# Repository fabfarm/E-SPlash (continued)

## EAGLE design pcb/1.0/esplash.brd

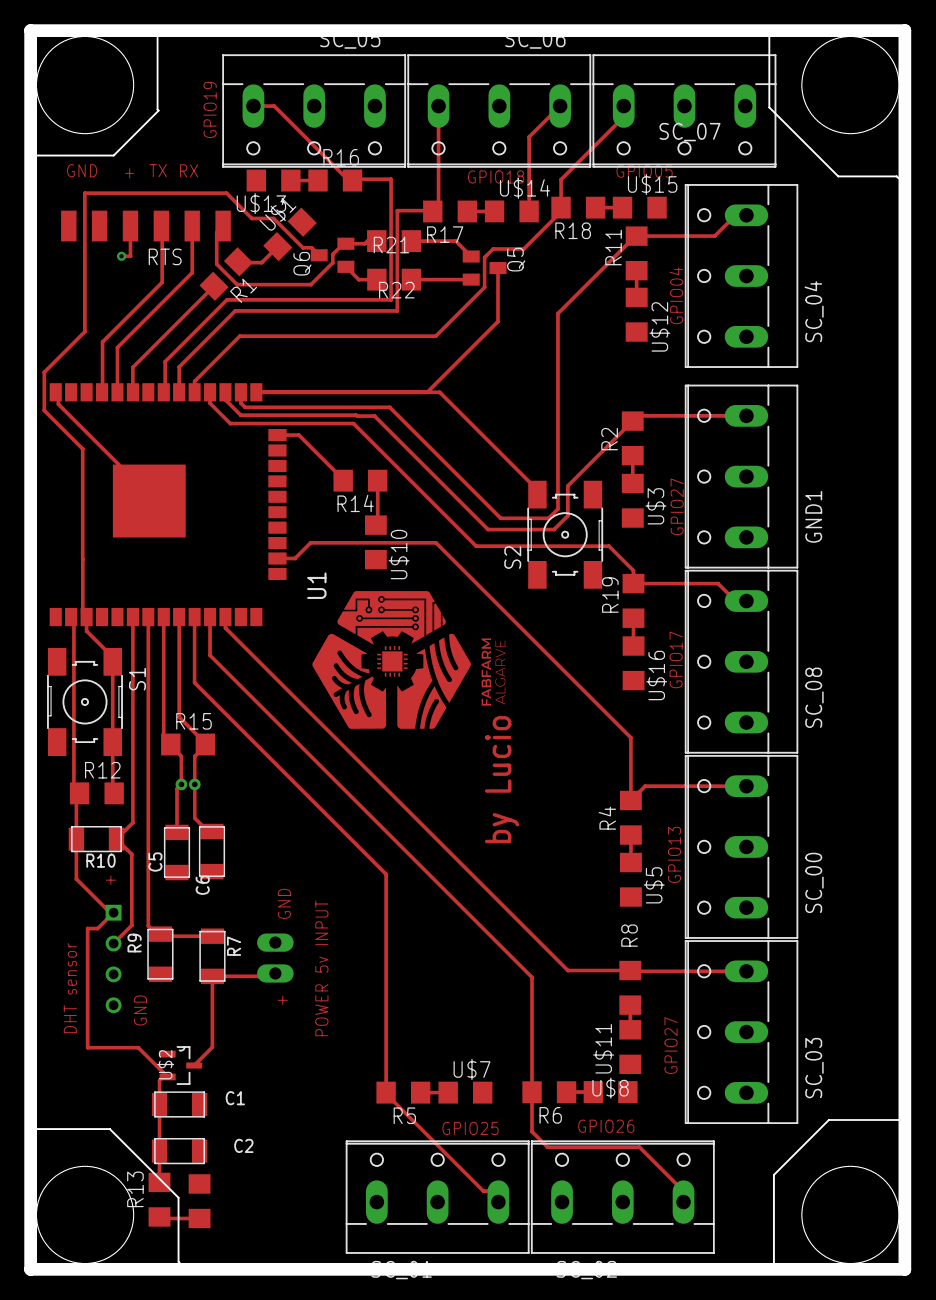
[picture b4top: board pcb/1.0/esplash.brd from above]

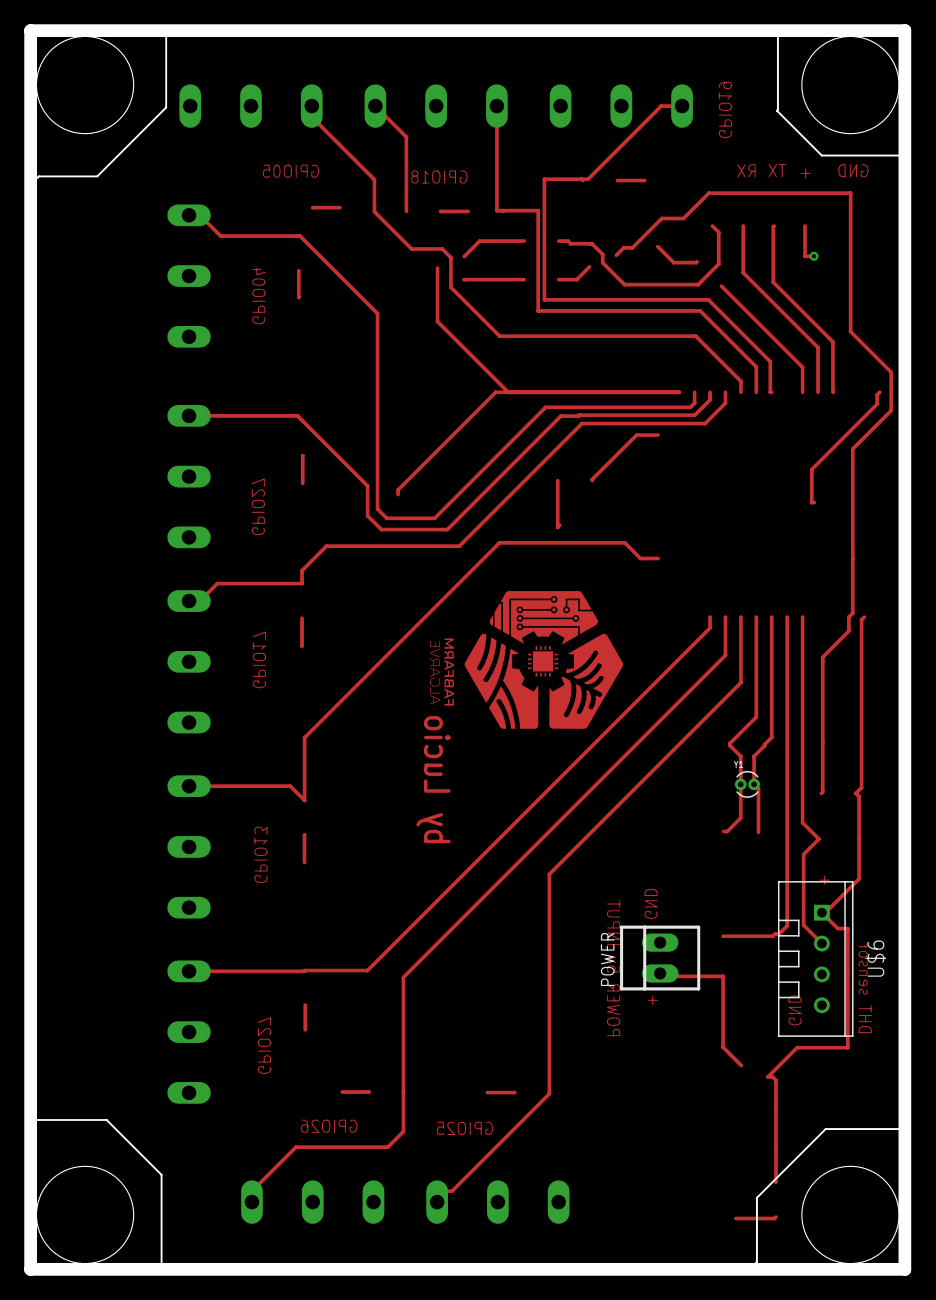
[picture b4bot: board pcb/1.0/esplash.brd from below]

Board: 2 copper layers, 72.0 x 102.0 mm, 57 parts (3 on the bottom side), 40 nets.

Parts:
C1: 100nF; C1206FAB
C2: 100uF; C1206FAB
C5, C6: 15pf; C1206FAB
GND1: SC; W237-103
POWER: 22-23-2021
Q5, Q6: BCX70SMD; SOT23
R1, R2, R4, R5, R6, R8, R11, R13, R14, R16, R17, R18, R19: 100ohm; R1206
R7: 1.2Mohm; R1206FAB
R9: 1.5Mohm; R1206FAB
R10: 10K; R1206FAB
R12, R15, R21, R22: 10k; R1206
RTS: FTDI-SMD-HEADER; 1X06SMD
S1: Reset; 6MM_SWITCH
S2: GPIO0 Button; 6MM_SWITCH
SC_00, SC_01, SC_02, SC_03, SC_04, SC_05, SC_06, SC_07, SC_08: SC; W237-103
U1: ESP-WROOM-32
U$1, U$3, U$5, U$7, U$8, U$9, U$10, U$11, U$12, U$13, U$14, U$15, U$16: LED; LED1206
U$2: MCP1700T-3302E/TT; SOT95P237X112-3N
U$6: TEMP-HUM-SENSOR-DHT11
Y1: ECS-.327-12.5-13X; XTAL_ECS-.327-12.5-13X

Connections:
3V3: C1.2, C2.1, R10.2, R12.1, R13.2, U1.2, U$2.2, U$6.1
32K_XN: C6.2, R15.2, U1.9, Y1.1
32K_XP: C5.2, R15.1, U1.8, Y1.2
CHIP_PU: Q6.3, R12.2, S1.1, S1.2, U1.3
DTR: Q5.2, R22.2
GND: C1.1, C2.2, C5.1, C6.1, GND1.1, POWER.2, R9.1, RTS.1, S1.3, S1.4, S2.3, S2.4, SC_00.1, SC_01.1, SC_02.1, SC_03.1, SC_04.1, SC_05.1, SC_06.1, SC_07.1, SC_08.1, U1.1, U1.15, U1.38, U1.GND, U$1.2, U$2.1, U$3.2, U$5.2, U$6.4, U$7.2, U$8.2, U$9.2, U$10.2, U$11.2, U$12.2, U$13.2, U$14.2, U$15.2, U$16.2
GPIO0: Q5.3, S2.1, S2.2, U1.25
GPIO1/TXD0: RTS.4, U1.35
GPIO02: R14.2, U1.24
GPIO3/RXD0: RTS.5, U1.34
GPIO4: R11.2, SC_04.3, U1.26
GPIO05/VALVE_RELAY07: R18.2, SC_07.3, U1.29
GPIO13/PUMP_RELAY: R4.2, SC_00.3, U1.16
GPIO16/CURRENT_SENSE: GND1.3, R2.2, U1.27
GPIO17/VALVE_RELAY08: R19.2, SC_08.3, U1.28
GPIO18/VALVE_RELAY06: R17.2, SC_06.3, U1.30
GPIO19/VALVE_RELAY05: R16.2, SC_05.3, U1.31
GPIO21/VALVE_RELAY04: R1.2, U1.33
GPIO25/VALVE_RELAY01: R5.2, SC_01.3, U1.10
GPIO26/VALVE_RELAY02: R6.2, SC_02.3, U1.11
GPIO27/VALVE_RELAY03: R8.2, SC_03.3, U1.12
GPIO34/DHT: R10.1, U1.6, U$6.2
GPIO35/BATTVOLT: R7.1, R9.2, U1.7
unnamed: R1.1, U$1.1
unnamed: R2.1, U$3.1
unnamed: R14.1, U$10.1
unnamed: R4.1, U$5.1
unnamed: R5.1, U$7.1
unnamed: R6.1, U$8.1
unnamed: R8.1, U$11.1
unnamed: R11.1, U$12.1
unnamed: R16.1, U$13.1
unnamed: R13.1, U$9.1
unnamed: Q5.1, R21.1
unnamed: R17.1, U$14.1
unnamed: R18.1, U$15.1
unnamed: R19.1, U$16.1
unnamed: Q6.1, R22.1
RTS: Q6.2, R21.2, RTS.6
VCC: GND1.2, POWER.1, R7.2, RTS.3, SC_00.2, SC_01.2, SC_02.2, SC_03.2, SC_04.2, SC_05.2, SC_06.2, SC_07.2, SC_08.2, U$2.3

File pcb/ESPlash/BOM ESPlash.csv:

Value,Coluna1,Package,Description,Qty,Unit Price,Total Price
PCB blank,,," Proto Board Copper Clad FR1, Single Sided, 1 oz. 5.00"" x 4.00"" (127.0mm x 101.6mm) ",1, $2.44 , $2.44 
FTDI-SMD-HEADER,,1X06SMD, CONN HEADER R/A 6POS 2.54MM ,1, $0.18 , $0.18 
22-23-2021,,22-23-2021, CONN HEADER VERT 2POS 2.54MM ,1, $0.17 , $0.17 
header2x6,,2X03, CONN HEADER VERT 6POS 2.54MM ,2, $0.48 , $0.96 
SWITCH,SWITCH,SWITCH TACTILE SPST-NO 50MA 12V,SWITCH TACTILE SPST-NO 50MA 12V,2, $0.20 , $0.40 
0.1uF ,Capacitor,C1206FAB, CAP CER 0.1UF 50V X7R 1206 ,2, $0.11 , $0.22 
100uF,Capacitor,C1206FAB, CAP CER 100UF 10V X5R 1206 ,1, $1.49 , $1.49 
15pf,Capacitor,C1206FAB, CAP CER 15PF 50V 1206 ,2, $0.19 , $0.38 
1nF,Capacitor,C1206FAB, CAP CER 1206 1NF 250V X7R 10% ,1, $0.27 , $0.27 
ESP32-WROOM-32 (16MB),,ESP-WROOM-32,WIFI MODULE 128MBITS SPI FLASH,1, $4.50 , $4.50 
LED,LED,LED1206,Standard LEDs - SMD 1206 Blue ,7, $1.45 , $10.15 
100ohm,Resistor,R1206,RES SMD 100 OHM 1% 1/4W 1206,5, $0.57 , $2.85 
10k,Resistor,R1206,RES SMD 10K OHM 1% 1/4W 1206,3, $0.57 , $1.71 
1.2Mohm,Resistor,R1206,RES SMD 1.2M OHM 1% 1/4W 1206,1, $0.10 , $0.10 
1.5Mohm,Resistor,R1206,RES SMD 1.5M OHM 1% 1/4W 1206,1, $0.18 , $0.18 
150ohm,Resistor,R1206,RES SMD 15 OHM 1% 1/4W 1206,2, $0.10 , $0.20 
1K,Resistor,R1206,RES SMD 1K OHM 1% 1/4W 1206,4, $0.57 , $2.28 
220omh,Resistor,R1206,RES SMD 220 OHM 1% 1/4W 1206,4, $0.10 , $0.40 
SRD-05VDC-SL-C,Relay,RELAY_SRD-05VDC-SL-C,SRD-5VDC-SL-C 5 Pin PCB Type,4, $1.99 , $7.96 
ACS712,,SO08, SENSOR CURRENT HALL 20A AC/DC ,1, $2.32 , $2.32 
,,SOD123, DIODE GEN PURP 100V 200MA SOD123 ,4, $0.13 , $0.52 
EL817(S)(D)(TU)-V,,SOIC254P1030X460-4N, OPTOISOLTR 5KV TRANSISTOR 4-DIP ,4, $0.18 , $0.72 
BCX70SMD,,SOT23, TRANS NPN 45V 0.1A SOT23 ,4, $0.19 , $0.76 
MCP1700T-3302E/TT,,SOT95P237X112-3N, IC REG LINEAR 3.3V 250MA SOT23-3 ,1, $0.37 , $0.37 
TEMP-HUM-SENSOR-DHT11,,TEMP-HUM-SENSOR-DHT11, SENSOR HUMID/TEMP 5V DTL 5% MOD ,1, $5.00 , $5.00 
,,W237-102,WAGO SCREW CLAMP,4, $0.10 , $0.40 
ECS-.327-12.5-13X,,XTAL_ECS-.327-12.5-13X,CRYSTAL 32.7680KHZ 12.5PF TH,1, $0.24 , $0.24 
,,,,, Total , $44.73

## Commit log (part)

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2020-06-14 new version compiling with external file system
2020-06-14 included code to show temp and humidity as well as time, all compiling
2020-06-15 Nnow we have time!
2020-06-16 function to turn time components like mins, hours etc into a variable
    I am still learning there must be an easier way :-)
2020-06-17 adding features into index.html. need help with JS bug
2020-06-18 Revert "Update README.md"
    This reverts commit 9f7c9a71d101eb58e78ddfe2259100fd16ccab90.
2020-06-18 Revert "updates"
    This reverts commit 29ba24a5f4c021fb44f9e41ddd7c0519eee81153.
2020-06-18 Revert "adding features into index.html. need help with JS bug"
    This reverts commit b84a338d112b8ed323edd0073b4a52574d56285e.
2020-06-20 Adding functions for get/save
2020-06-20 Adds AsyncJson to platform.io Not yet in use but may use for handling json server side
2020-06-21 POC for json serialize / deserialize
2020-06-21 Write json to disk Read json from disk Deserialize json & update values
2020-06-21 Proof of concept for json
2020-06-21 change data.jaon
    added states
2020-06-21 Callback work in progress
2020-06-21 json read/write
    SPIFFS having trouble with r/w file system
2020-06-22 Backend working
2020-06-22 html reading json
    - html file + js building page from json
2020-06-22 works
2020-06-23 some cleanning up
2020-06-23 Update formatting & comments
2020-06-23 Update formatting + comments
2020-06-23 fix typo
2020-06-23 fix bugs introduced from merges
2020-06-23 manual mode and schedule mode works now.
2020-06-24 progress save on scheduling
    need to break apart time and compare to current time
2020-06-24 last update of the night
2020-06-25 updates
    sucssessifully parsing the json to c++ already in int for the start time and duration
    matrix logic test tested! its good prints well all parameters
    next is to make the start logic
2020-06-26 dealing with issue #10
    -changed from while to if (WiFi.status() != WL_CONNECTED) and placed in the loop instead of setup adding a message for the case it connected.
    Tested i my setup it works.
    -added message of wich sone is active.
2020-06-26 now #6 is fixed
2020-06-27 #11 attempt to add pump on/offalong with valves
    - included pumpPin 33 and its declarations
    - Included digitalWrite on each case
    - modified names from override to isScheduleMode
    ps: its not working as expected, the pumpPin keps going low ... high ... low... high
    @jknight I know its bad code, need to sleep, will leave here safe at the hands of github...
2020-06-27 #14 removed unecessary reading of json...
2020-06-28 #11 Pump now enable / disables as expected.
2020-06-30 short delays
2020-07-02 PCB updates
2020-07-06 board
2020-07-16 creating enclosure
2020-11-02 remove delays
2021-04-29 trying to fix wifi bug and refresh bug
2021-04-30 Adding time without using internet
2021-05-01 PCB changes
2021-05-07 Html/ json communication fail
2021-05-10 new board
2021-05-10 update monitor speed
2021-05-11 Update fabfarm_irrigation.ino
    Changes suggested by @carlosmouracorreia in his commit 7e49d787ab5b9ebbfad36f8027c647d13e586848
2021-05-14 Solved the freezing time problem but need to reset each time the time is modified (to be improved)
2021-05-17 no freezing time without external declaration
    but still needs to reset for time change
2021-05-21 improving relay table in settup page
    improving relay table in settup page and updating sample json
2021-07-04 added support for relays with TTL Logic LOW and cleanup
    included option to use relays with TTL Logic LOW
    improve readability and cleanup
2021-07-19 adding support for DS3231
    Adding support for DS3231 and cleaning up
2021-07-25 separating java script from html and having fonts locally
2021-07-26 refreshing the time every second. side effect is that the slider is not as smooth. next step separate the script so only update what is needed.
2021-07-26 added function to write first json file in case it does not exist.
    added function to write data.json file in case it does not exists,
    It uses the file sample.json to create a first data.json file.
2021-08-04 small changes not tested
2021-08-20 test
2021-08-21 clean up old code
2021-08-24 fixing wifi bug that prevented from being connected from a smartphone
2021-08-24 created pcb profiles with if def and clean up code
    created pcb profiles with if def and clean up code removing function previously used to reconnect
2021-09-14 reduction of web page refresh rate from 1s to 10s and fix of the /getdata route by using a copy of jsondocument to serialize instead of a cast
2021-09-16 correcting parameters of prototype board
2021-09-19 Added a few credentials for wifi and changed DHT sensor settings
2022-02-07 (#0) Add properties
2022-02-14 (#0) Finish control page times basic feature. Still need validations
2022-02-25 (#0) Add funcitonailties
2022-03-03 Code review, consistent function names and documentation
2022-03-04 added ifdef for stactic IP
    added ifdef for stactic IP also removed a done todo
2022-03-07 Refactor WiFi configuration
2022-03-08 comments clearification.
2022-03-10 Move to a more RESTful Web API, improved refresh
    Use more REST aware endpoints
    Moved Scheduling Mode HTML element from JavaScript into the HTML file
    Use more REST aware endpoints
    Rewritten refresh method, tries to update live state with the least
    possible delay
2022-03-10 HTML validation results, local bootstrap
    Validated the HTML with w3c.org HTML Checker and solved found errors.
    Bootstrap library is now hosted from device, and not from Content
    Delivery Network.
    Moved Scheduling Mode HTML element from JavaScript into the HTML file
2022-03-10 Initial config.json file for future use
2022-03-10 Move to a more RESTful Web API
    Use more REST aware endpoints
2022-03-10 Fix rendering the relay times
2022-03-10 Move to Bootstrap, work in progress
2022-03-10 Improved serial print
2022-03-18 Fix and rework time scheduling code
2022-03-25 Fix bug in setting scheduling mode
2022-05-26 set lib versions in working versions
2022-05-27 fixed typo jason -> json
2022-06-16 adding multi wifi support
2022-06-24 change to battery sensing board
2023-02-19 better comments and struct for board selection
    modified board selection with struct to improve understanding of the code. improved and added comments
2023-02-19 JS updates
2023-06-14 resolve compileerror
2023-06-15 refactor WebServerHandle.cpp
2023-06-16 refactor WiFiHandler.cpp
2023-06-19 modify for litleFS, fix bug, refactor jsonHandler
2023-06-23 include elegantOTA
2023-06-23 increase time interval to refresh data
2023-07-10 resetting vite template
2023-07-10 Add main components
2023-07-10 add logo + testing github login
2023-07-10 Header comp; add logo; comp indexes;
2023-07-10 minor
2023-07-10 some dashboard styles
2023-07-11 test other reset libs
2023-07-11 tablet breakpoint
2023-07-11 sanitize.css; more styles;
2023-07-11 basic controls style and html
2023-07-11 more styles
2023-07-11 logo responsiveness
2023-07-12 add automatic time inputs
2023-07-12 removed individual manual-auto
2023-07-13 add Home page
2023-07-13 topbar router links
2023-07-16 controlsData; handle schedule mode checkbox;
2023-07-17 styling
2023-07-17 handleToggleRelay: updating state in nested object finally work
2023-07-18 WIP: set time btn onclick
2023-07-20 comments on functions to look at
2023-07-20 basic DateAndTime html and css
2023-07-20 wifi credentials html
2023-07-24 fetchSettingsData; updateTime and enableInternetUpdate
2023-07-24 WifiCredentials: updateCredentials;
2023-07-25 api-schema and data - WIP
2023-07-25 more api-schema - WIP
2023-07-25 mods and comments for new relay contro lbox design
2023-07-26 going back to orginal design
2023-07-26 star working on Settings page baased on old server
2023-07-26 fetch data - wip; services - wip;
2023-07-26 dashboard uses new data structure
2023-07-26 methods based on api-schema - WIP
2023-07-26 methods based on api-schema
2023-07-27 Relays
2023-07-28 api-schema and notes
2024-04-16 Temporary hotfix for ISR timeout until MR for ISR timeout with latest updates is available
2024-04-17 gitignore changes
2024-04-23 moving from AsyncElegantOTA to ElegantOTA due to the first is discontinued
2025-02-01 add version to arduinoJson to prevent breaking changes
2025-06-29 Hardware configuration cleanup: hard-coded relay pins in platformio.ini and simplified board config
    - Added relay pins as build flags: RELAY1_PIN=27, RELAY2_PIN=26, RELAY3_PIN=25, PUMP_PIN=13
    - Simplified BoardConfig to single configuration without hardware variants
    - Updated sample.json to use correct relay pins (27, 26, 25)
    - Ready for further simplification of relay management UI
2025-06-29 Add AI coding guidelines for project architecture
    - Emphasizes keeping main.cpp clean and modular
    - Prohibits delay() functions on ESP32 with web servers
    - Documents fixed hardware pin configuration
    - Establishes clear modular architecture rules
    - Provides specific do's and don'ts for future AI assistants
2025-06-29 Remove unused pin definitions from platformio.ini
    - Removed I2C_SDA_PIN and I2C_SCL_PIN (unused, I2C pins hardcoded in Config.cpp)
    - Removed RTC_IRQ_PIN (unused, no interrupt handling)
    - Removed BAT_VOLT_PIN (unused, no battery voltage monitoring)
    - Removed NUM_RELAYS (unused in codebase)
    - Simplified configurations to only include necessary GPIO pins for relay control
2025-06-29 Remove pin configuration from JSON - use hardcoded hardware pins
    - Removed initializeHardwarePins() function from JsonHandler
    - Updated RelayHandler to use hardcoded pins (RELAY1_PIN, RELAY2_PIN, RELAY3_PIN)
    - Removed pin fields from sample.json since pins are hardware-specific
    - Pins are now defined in platformio.ini and cannot be changed by users
    - This prevents configuration conflicts and enforces hardware constraints
2025-06-29 Optimize scheduling system with event-driven approach
    - Implement event-driven scheduling to eliminate serial output flooding
    - Add getNextScheduleEventTime() function to calculate next schedule events
    - Replace constant schedule checking with smart event-based triggers
    - Add state tracking to prevent redundant relay operations and logging
    - Implement smart frontend polling (10s/60s intervals based on schedule proximity)
    - Remove debug output spam from WebServerManager handleGetDataJsonRequest
2025-06-30 Remove OTA functionality from irrigation system
    - Deleted OTAHandler.h and OTAHandler.cpp files
    - Removed OTA includes from Config.h
    - Removed initializeOTA() and handleOTA() calls from main.cpp
    - Removed ArduinoOTA library dependency from platformio.ini
    - Simplified main loop by removing OTA active checks
    - Project now compiles successfully without OTA functionality
2025-06-30 feat: Complete UI redesign with modern agricultural theme and enhanced functionality
    🎨 Design Improvements:
    - Implemented modern glass-morphism design with agricultural gradient background
    - Large prominent logo with white background for better visibility
    - Consistent design language across main page and setup page
    - Mobile-first responsive design optimized for phone screens
    - Professional typography with proper visual hierarchy
2025-08-11 Refactor and modernize the frontend UI.
    This commit overhauls the user interface of the web application served by the ESP32. The changes include:
    - Consolidating all CSS styles into a single, unified stylesheet (`modern-style.css`).
    - Removing inline styles from `index.html`.
    - Extracting inline JavaScript from `setuppage.html` into a separate `setup.js` file.
    - Modernizing the JavaScript to use the `fetch` API instead of the older `XMLHttpRequest`.
    - Updating all asset paths to be relative, ensuring compatibility with file-based viewing for testing.
